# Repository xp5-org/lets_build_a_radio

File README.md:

# make a radio project
describe a goal centered on a task or a component, organize people interested in the design and or build process

<br>

[discord link](https://discord.gg/Xgx8TTps)

<br>

## 1) AD9854 TX ONLY SDR
- using AD9854ASTZ DDS to generate SSB/AM/FM from 1 to 30mhz
- want to pair to RP2350 / PI PICO 2 for simplicity
- class-A amplifier to make output useable
- build it as a hobby learning tool
optionally : add on AD9200 10-bit ADC for rx support (lots of extra work)

## 2) Class-E 2200M 137KHZ oscillator
- simple N-mosfet class E transmitter to experiment with
  (files not uploaded yet)

<br>
<br>
<br>

## general process of turning an idea into a board

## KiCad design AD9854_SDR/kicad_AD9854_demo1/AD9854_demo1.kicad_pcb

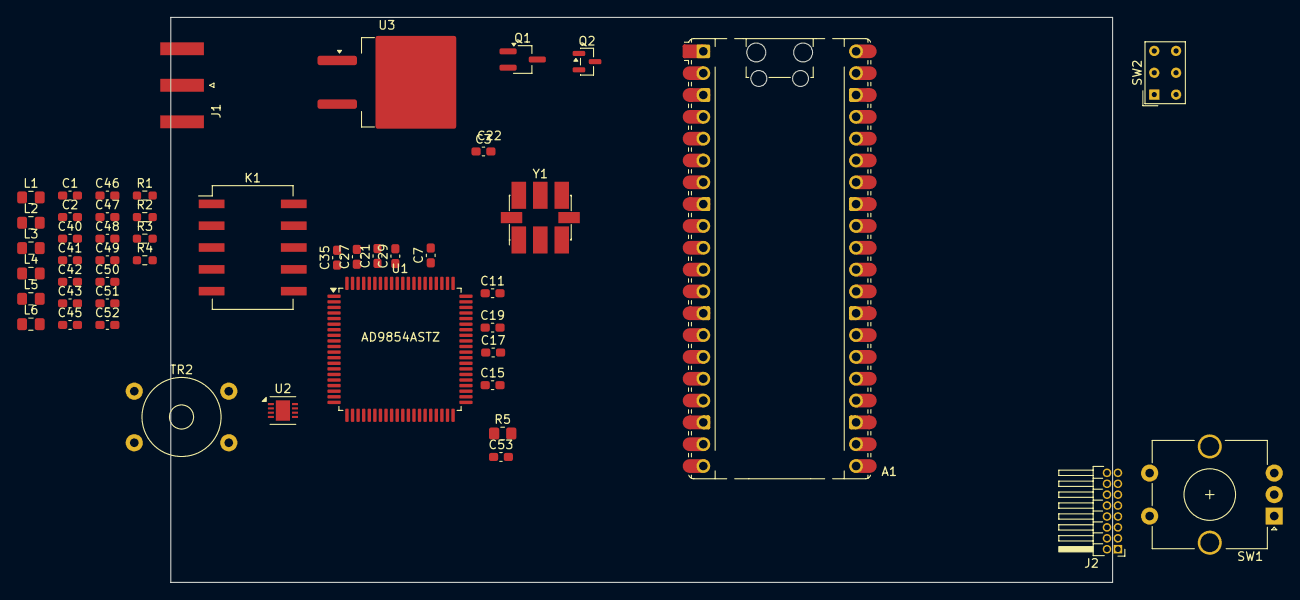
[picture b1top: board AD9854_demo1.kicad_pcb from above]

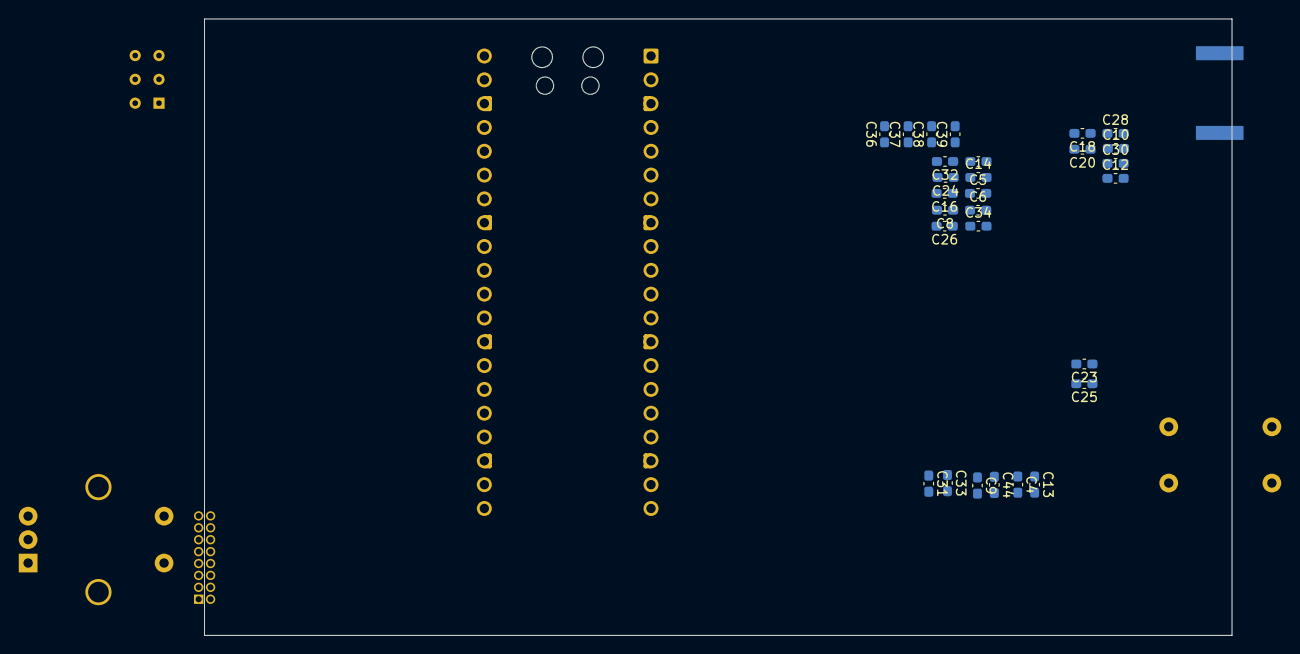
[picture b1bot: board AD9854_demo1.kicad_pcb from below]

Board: 2 copper layers, 109.6 x 65.8 mm, 77 parts (28 on the bottom side), 18 nets, no tracks yet.

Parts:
A1: RaspberryPi_Pico; RaspberryPi_Pico_Common_Unspecified
C1, C2, C40, C41, C42, C43, C45, C46, C47, C48, C49, C50, C51, C52: C; C_0603_1608Metric_Pad1.08x0.95mm_HandSolder
C3, C4, C7, C9, C11, C13, C15, C17, C19, C21, C23, C25, C27, C29, C31, C33, C35, C36, C37, C38, C39: 0.1uF; C_0603_1608Metric_Pad1.08x0.95mm_HandSolder
C5, C6, C8, C10, C12, C14, C16, C18, C20, C22, C24, C26, C28, C30, C32, C34, C44: 10uF; C_0603_1608Metric_Pad1.08x0.95mm_HandSolder
C53: 0.01uF; C_0603_1608Metric_Pad1.08x0.95mm_HandSolder
J1: Conn_Coaxial_Small; SMA_Amphenol_132289_EdgeMount
J2: Conn_02x08_Row_Letter_First; PinHeader_2x08_P1.27mm_Horizontal
K1: G6H-2; Relay_DPDT_Omron_G6H-2F
L1, L2, L3, L4, L5, L6: L; L_0805_2012Metric_Pad1.15x1.40mm_HandSolder
Q1: AO3401A; SOT-23W_Handsoldering
Q2: AO3400A; SOT-23
R1, R2, R3, R4: R; R_0603_1608Metric_Pad0.98x0.95mm_HandSolder
R5: 3900; R_0805_2012Metric_Pad1.20x1.40mm_HandSolder
SW1: RotaryEncoder_Switch_MP; RotaryEncoder_Alps_EC12E-Switch_Vertical_H20mm_CircularMoun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
SW2: SW_NKK_GW12LJPCF; SW_NKK_GW12LJP
TR2: TRANSF3; Transformer_Toroid_Horizontal_D9.0mm_Amidon-T30
U1: AD9854ASTZ; LQFP-80_14x14mm_P0.65mm
U2: LT5560; DFN-8-1EP_3x3mm_P0.5mm_EP1.66x2.38mm
U3: MCP1826ST-3302E/EB; TO-263-2_TabPin1
Y1: Si570; Oscillator_SMD_SI570_SI571_HandSoldering

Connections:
3.3v_AVDD: C4.1, C7.1, C9.1, C11.1, C13.1, C15.1, C17.1, C19.1, C44.1, U1.31 (AVDD), U1.32 (AVDD), U1.37 (AVDD), U1.38 (AVDD), U1.44 (AVDD), U1.50 (AVDD), U1.54 (AVDD), U1.60 (AVDD), U1.64 (DIFFCLKENABLE), U1.65 (AVDD), U1.70 (S/P_SELECT)
3.3v_DVDD: C21.1, C23.1, C25.1, C27.1, C29.1, C31.1, C33.1, C35.1, U1.9 (DVDD), U1.10 (DVDD), U1.23 (DVDD), U1.24 (DVDD), U1.25 (DVDD), U1.73 (DVDD), U1.74 (DVDD), U1.79 (DVDD), U1.80 (DVDD)
3v_ldo: C5.1, C6.1, C8.1, C10.1, C12.1, C14.1, C16.1, C18.1, C20.1, C22.1, C24.1, C26.1, C28.1, C30.1, C32.1, C34.1, C36.1, C37.1, C38.1, C39.1, Y1.6 (Vcc)
GND: C1.2, C3.1, C4.2, C5.2, C6.2, C7.2, C8.2, C9.2, C10.2, C11.2, C12.2, C13.2, C14.2, C15.2, C16.2, C17.2, C18.2, C19.2, C20.2, C21.2, C22.2, C23.2, C24.2, C25.2, C26.2, C27.2, C28.2, C29.2, C30.2, C31.2, C32.2, C33.2, C34.2, C35.2, C36.2, C37.2, C38.2, C39.2, C42.2, C43.2, C44.2, C45.2, C46.2, C48.2, C50.2, C52.2, C53.2, R1.2, R2.2, R3.2, R4.2, R5.2, TR2.4, U1.11 (DGND), U1.12 (DGND), U1.26 (DGND), U1.27 (DGND), U1.28 (DGND), U1.33 (AGND), U1.34 (AGND), U1.39 (AGND), U1.40 (AGND), U1.41 (AGND), U1.45 (AGND), U1.46 (AGND), U1.47 (AGND), U1.53 (AGND), U1.59 (AGND), U1.62 (AGND), U1.66 (AGND), U1.67 (AGND), U1.72 (DGND), U1.75 (DGND), U1.76 (DGND), U1.77 (DGND), U1.78 (DGND), Y1.3 (GND)
I_out_A: C1.1, C2.1, L2.1, U1.52 (IOUT2)
I_out_B: R1.1, U1.51 (IOUT2*)
Lowpass_I_out_A: C41.2, C45.1, L3.2
Lowpass_Q_out_A: C51.2, C52.1, L6.2, TR2.3
unnamed: A1.3 (GND), A1.8 (GND), A1.13 (GND), A1.18 (GND), A1.23 (GND), A1.28 (GND), A1.38 (GND)
unnamed: C2.2, C40.1, C42.1, L1.1, L2.2
unnamed: C40.2, C41.1, C43.1, L1.2, L3.1
unnamed: C47.2, C48.1, C49.1, L4.2, L5.1
unnamed: C49.2, C50.1, C51.1, L5.2, L6.1
unnamed: C53.1, U1.55 (DACBP)
Q_out_A: C46.1, C47.1, L4.1, U1.48 (IOUT1)
Q_out_B: R2.1, U1.49 (IOUT1*)
diffclockA: R3.1, U1.69 (REFCLK), Y1.4 (CLK+)
diffclockB: C3.2, R4.1, U1.68 (REFCLK*), Y1.5 (CLK-)

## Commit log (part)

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2026-04-27 adding things
    init
2026-04-27 moved
2026-04-29 add files
    adding ltspice examples & python tools
2026-06-25 more
